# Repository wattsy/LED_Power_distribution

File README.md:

# LED_Power_distribution
LED Power distribution

Ouput connectors
2 Pin 5.08mm Straight Screw Terminal Block Connector
https://www.aliexpress.com/item/1005002951707517.html?spm=a2g0o.cart.0.0.6ce538da4Un4fh&mp=1&pdp_npi=6%40dis%21AUD%21AUD+2.82%21AUD+2.59%21%21AUD+2.51%21%21%21%402101e80f17797789895532980efb21%2112000022934449585%21ct%21AU%21728683763%21%218%210%21

Input Connector
Screw Terminal Block Connector Black Green 7.62mm Pitch
https://www.aliexpress.com/item/32843271485.html?spm=a2g0o.cart.0.0.6ce538da4Un4fh&mp=1&pdp_npi=6%40dis%21AUD%21AUD+0.48%21AUD+0.48%21%21AUD+0.48%21%21%21%402101e80f17797789895532980efb21%2167234824209%21ct%21AU%21728683763%21%212%210%21

LED
3mm LED
https://www.aliexpress.com/item/1005003320140965.html?spm=a2g0o.detail.0.0.2db9kReekReeUJ&mp=1&pdp_npi=6%40dis%21AUD%21AUD+4.80%21AUD+4.80%21%21AUD+4.66%21%21%21%402103123917798748920725808ecad1%2112000025195201401%21ct%21AU%21728683763%21%211%210%21

Resistor
1Kohm 1/4w Carbon Film Resistor
https://www.aliexpress.com/item/1005002369567811.html?spm=a2g0o.detail.0.0.46aatFV0tFV0Zr&mp=1&pdp_npi=6%40dis%21AUD%21AUD+1.65%21AUD+1.65%21%21AUD+1.57%21%21%21%402103123917798749497986736ecad1%2112000020363092336%21ct%21AU%21728683763%21%211%210%21&pdp_ext_f=%7B%22cart2PdpParams%22%3A%7B%22pdpBusinessMode%22%3A%22retail%22%7D%7D

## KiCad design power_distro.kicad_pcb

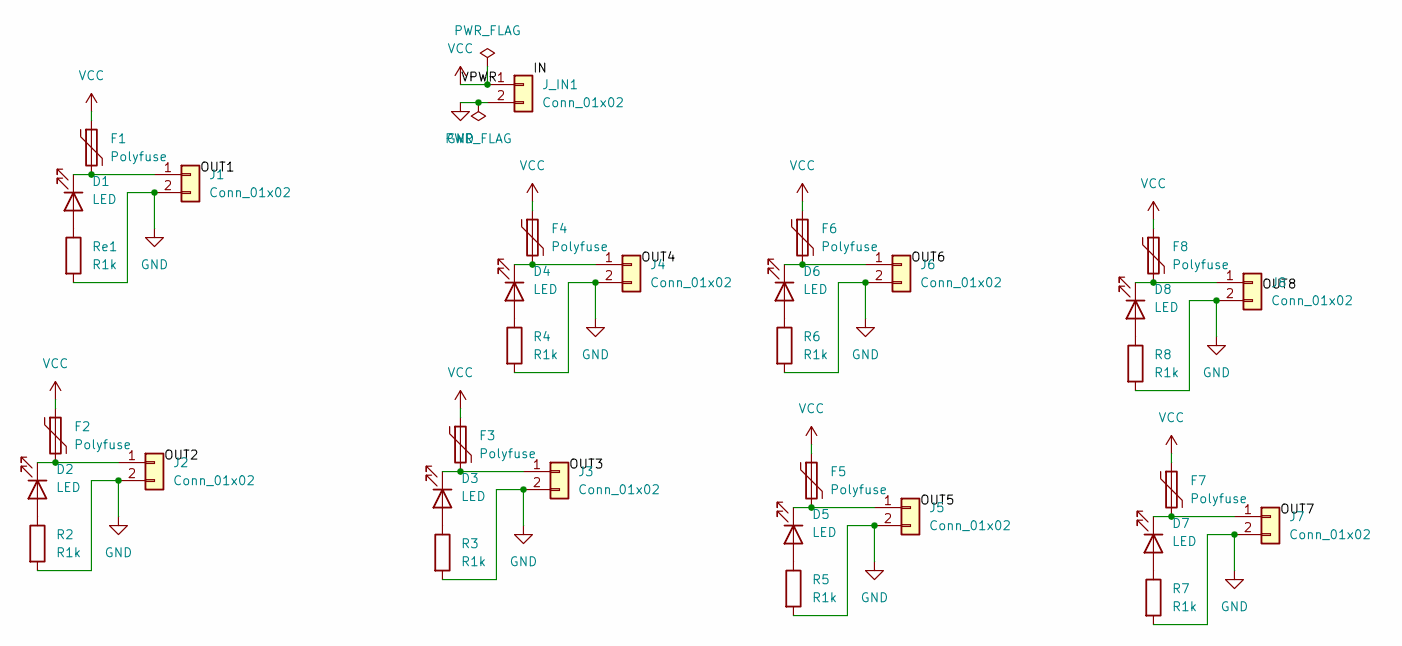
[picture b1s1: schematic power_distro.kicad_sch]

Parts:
D1, D2, D3, D4, D5, D6, D7, D8: LED; LED_D3.0mm
F1, F2, F3, F4, F5, F6, F7, F8: Polyfuse; Fuse_Bourns_MF-RHT1000
J1, J2, J3, J4, J5, J6, J7, J8: Conn_01x02; PhoenixContact_MSTBVA_2,5_2-G-5,08_1x02_P5.08mm_Vertical
J_IN1: Conn_01x02; TerminalBlock_MetzConnect_Type171_RT13702HBWC_1x02_P7.50mm_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
R2, R3, R4, R5, R6, R7, R8: R1k; R_Axial_DIN0207_L6.3mm_D2.5mm_P2.54mm_Vertical
Re1: R1k; R_Axial_DIN0207_L6.3mm_D2.5mm_P2.54mm_Vertical

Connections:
GND: J1.2, J2.2, J3.2, J4.2, J5.2, J6.2, J7.2, J8.2, J_IN1.2, R2.2, R3.2, R4.2, R5.2, R6.2, R7.2, R8.2, Re1.2
unnamed: D1.2 (A), Re1.1
unnamed: D1.1 (K), F1.2, J1.1
unnamed: D2.2 (A), R2.1
unnamed: D2.1 (K), F2.2, J2.1
unnamed: D3.2 (A), R3.1
unnamed: D3.1 (K), F3.2, J3.1
unnamed: D4.2 (A), R4.1
unnamed: D4.1 (K), F4.2, J4.1
unnamed: D5.2 (A), R5.1
unnamed: D5.1 (K), F5.2, J5.1
unnamed: D6.2 (A), R6.1
unnamed: D6.1 (K), F6.2, J6.1
unnamed: D7.2 (A), R7.1
unnamed: D7.1 (K), F7.2, J7.1
unnamed: D8.2 (A), R8.1
unnamed: D8.1 (K), F8.2, J8.1
VCC: F1.1, F2.1, F3.1, F4.1, F5.1, F6.1, F7.1, F8.1, J_IN1.1

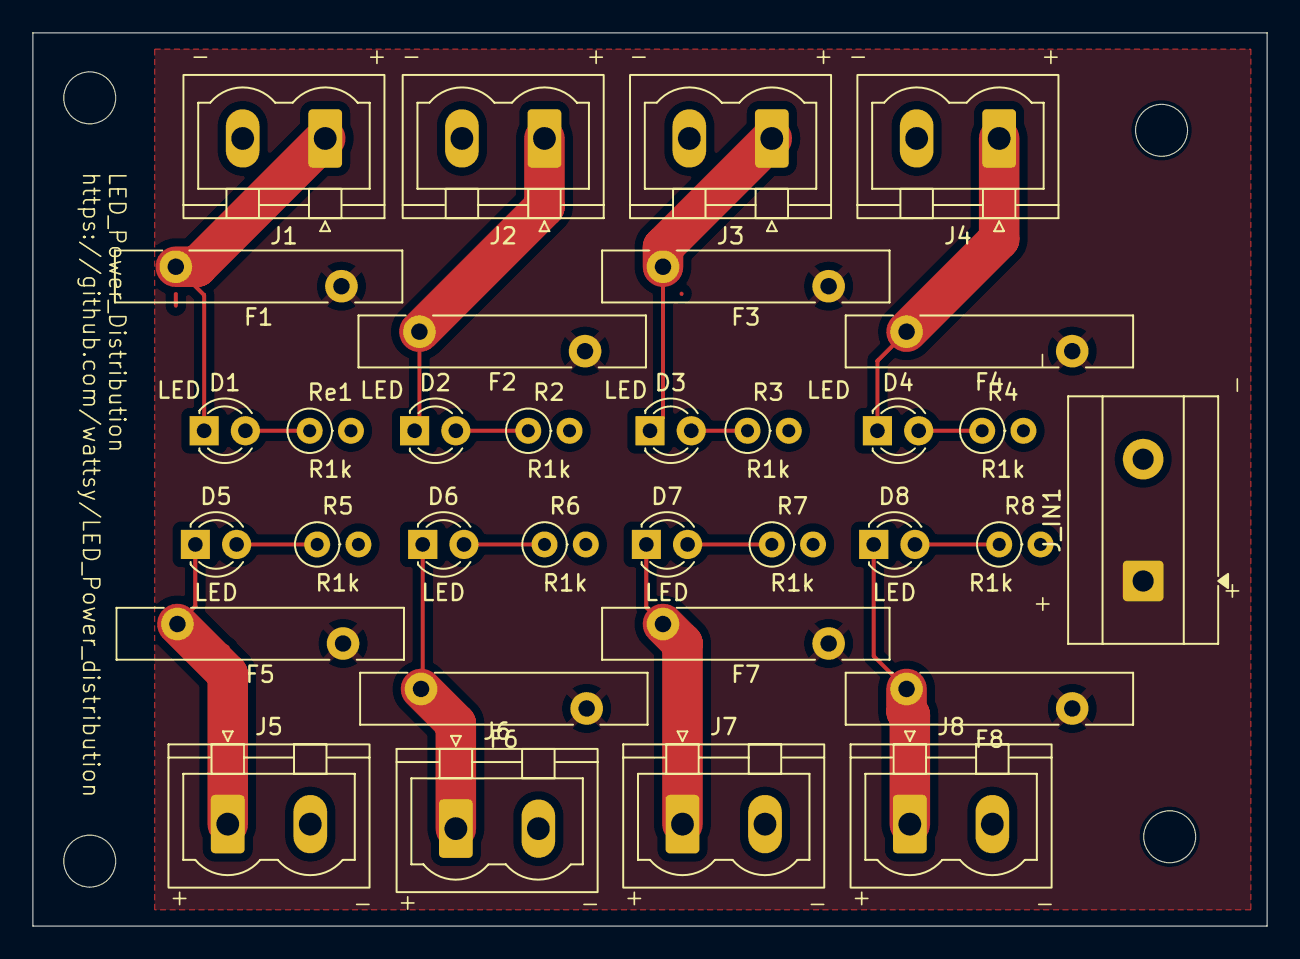
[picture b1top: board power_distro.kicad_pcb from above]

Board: 2 copper layers, 76.0 x 55.0 mm, 33 parts (0 on the bottom side), 18 nets.

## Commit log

2026-05-19 Updated_mask
2026-05-19 remove_not_needed labels
2026-05-19 bring labels to silkscreen
2026-05-19 change power in connector
2026-05-19 schema change
2026-05-27 update rotation of connectors
2026-05-27 add +- on input
2026-05-27 Update README with component details and links
    Added details about output and input connectors, LEDs, and resistors with links.
2026-06-25 update for PTC
2026-06-25 Update README with component details and images
    Added images and additional details for components.
2026-06-25 further PTC update
